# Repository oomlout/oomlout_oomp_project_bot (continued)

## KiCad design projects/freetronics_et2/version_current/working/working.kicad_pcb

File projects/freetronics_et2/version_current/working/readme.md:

# ET2 by freetronics  
This is a harvested standardized copy of a project from github.  
The original project can be found at:  
https://github.com/freetronics/ET2  
Please consult that link for additional, details, files, and license information.  
Note: It was auto harvested and if the original repo had more than one board file or anything out of the ordinary the files here are likely not representative.

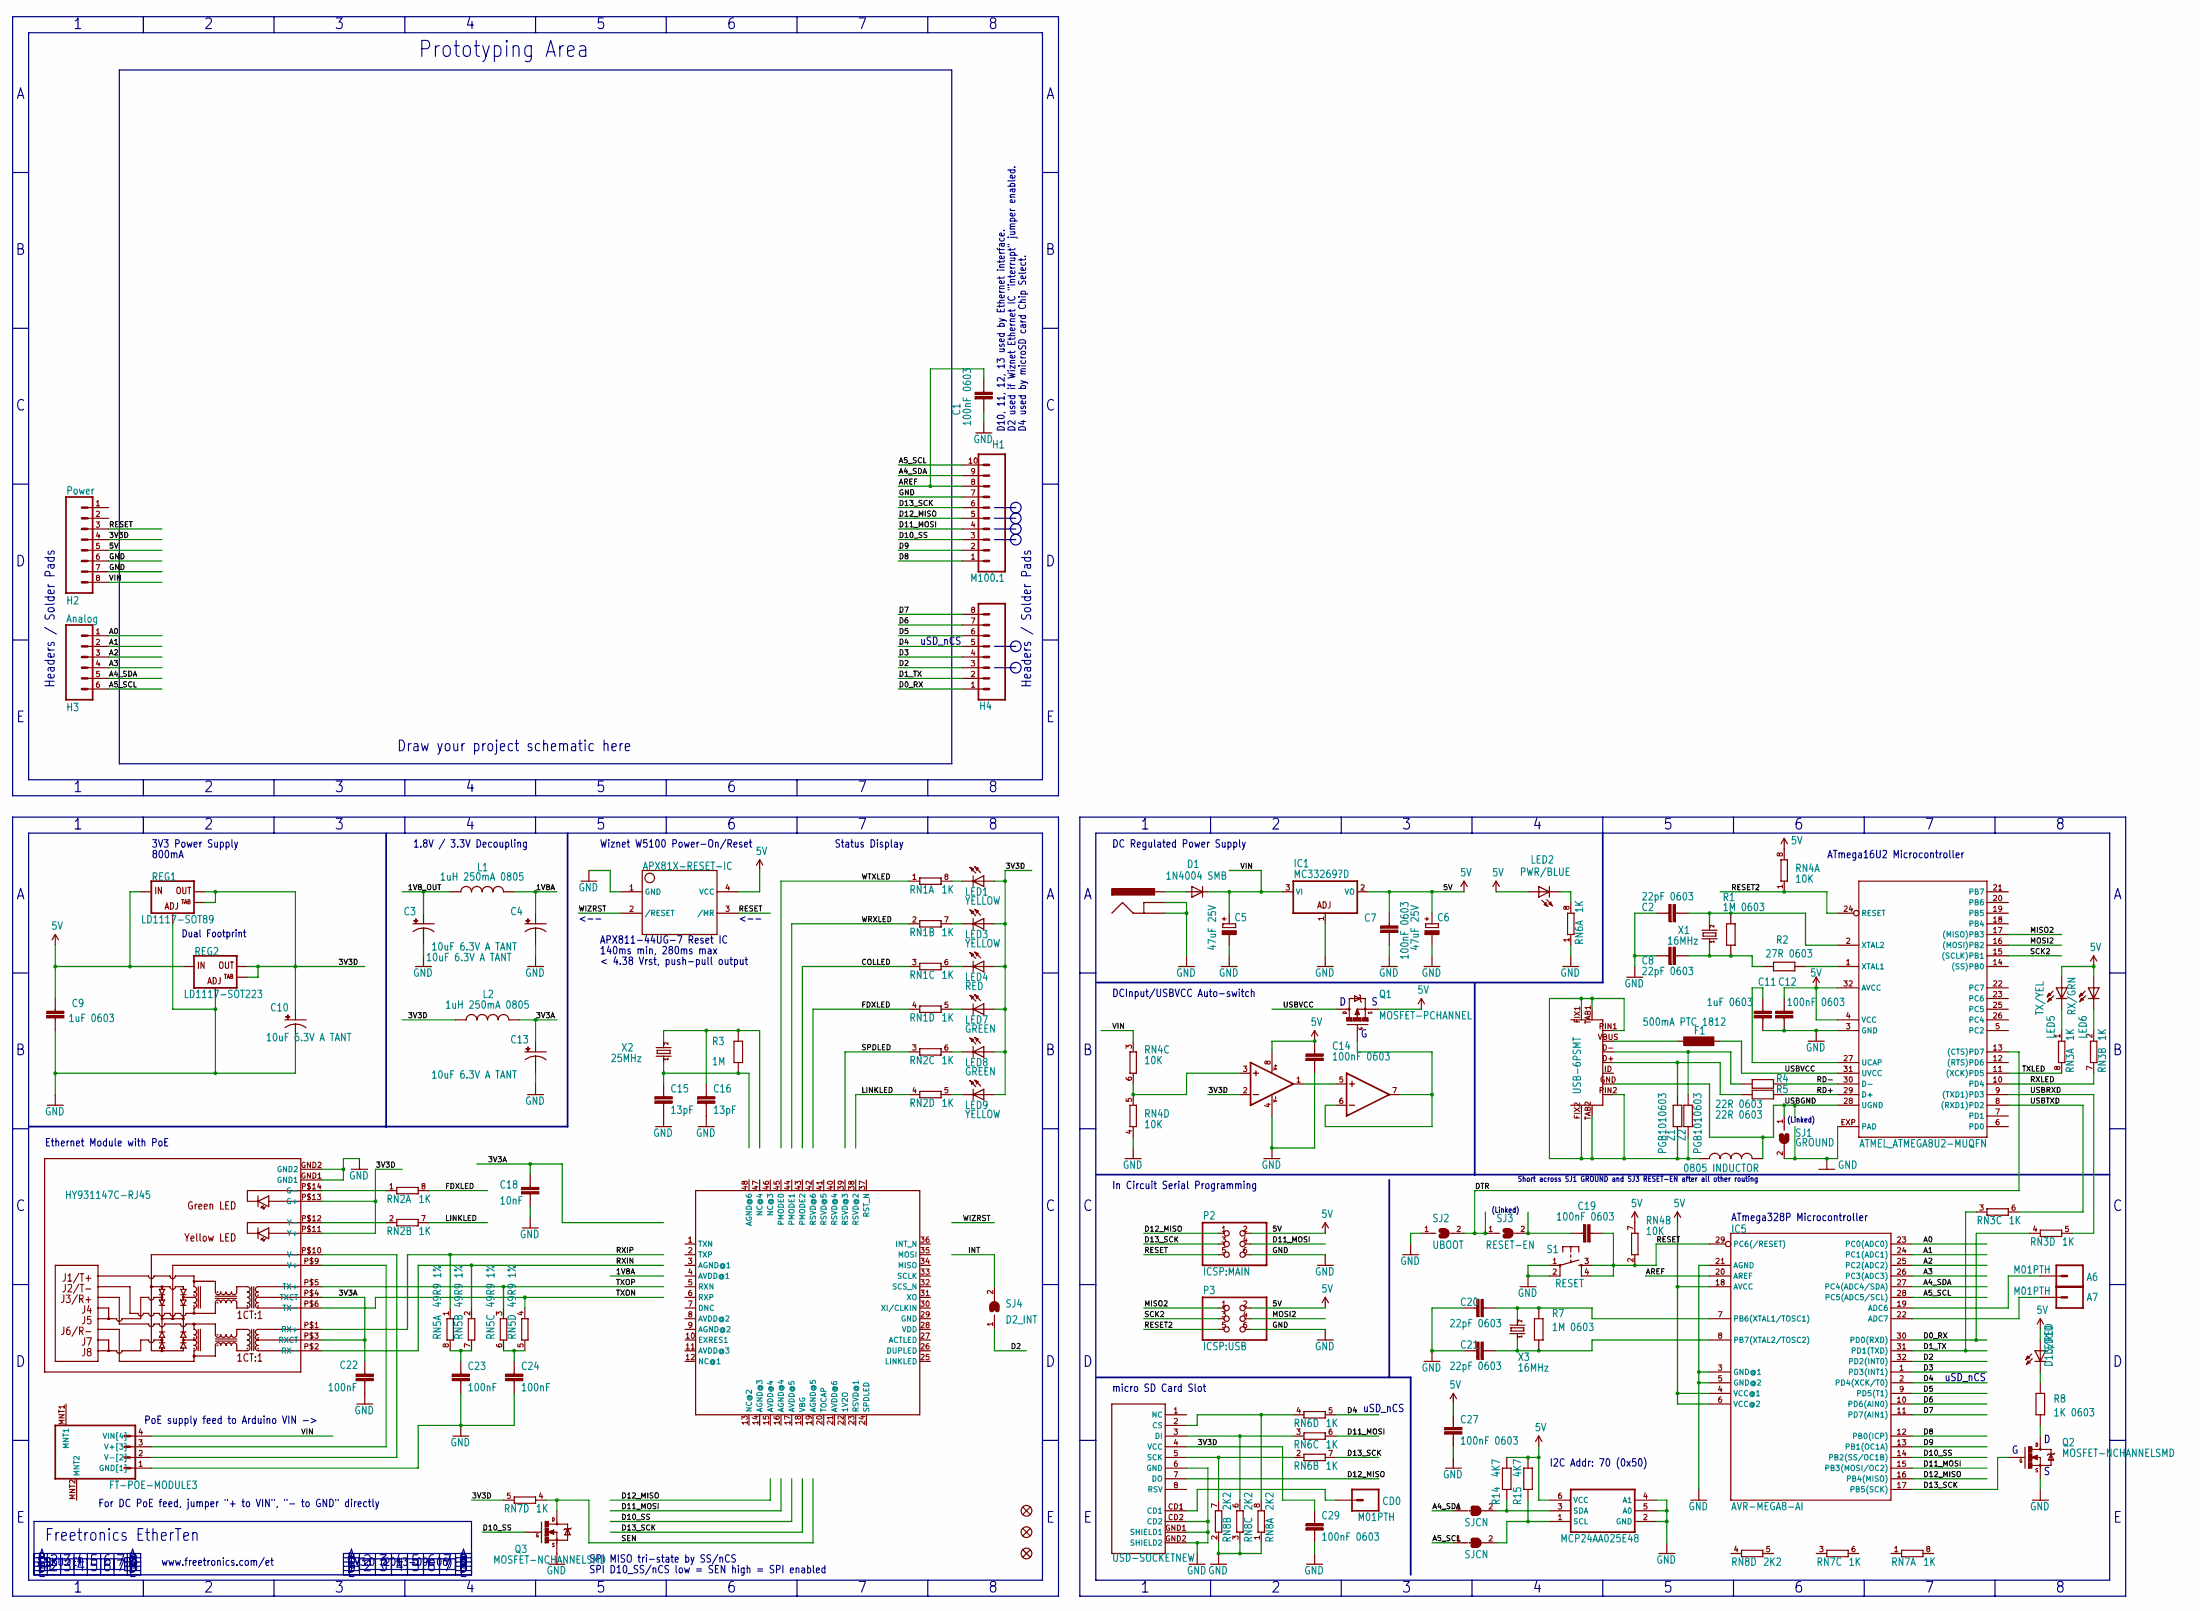
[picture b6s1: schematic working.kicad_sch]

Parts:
A6, A7: M01PTH; 1X01
C1, C7, C12, C14, C19, C27, C29: 100nF 0603; 0603
C2, C8, C20, C21: 22pF 0603; 0603
C3, C4, C10, C13: 10uF 6.3V A TANT; EIA3216
C5, C6: 47uF 25V; PANASONIC_D
C9, C11: 1uF 0603; 0603
C15, C16: 13pF; 0603
C18: 10nF; 0603
C22, C23, C24: 100nF; 0603
CD0: M01PTH; 1X01
D1: 1N4004 SMB; SMB-DIODE
F1: 500mA PTC 1812; L1812
FID1, FID2, FID3: FIDUCIAL1X2.5; FIDUCIAL-1X2.5
H1: M100.1; 1X10
H2: Power; 1X08
H3: Analog; 1X06
H4: Digital_0_7; 1X08
IC1: MC33269?D; DPACK
IC2: APX81X-RESET-IC; SOT143-R
IC3: ATMEL_ATMEGA8U2-MUQFN; ATMEL_QFN32
IC4: LM358D; SO08
IC5: AVR-MEGA8-AI; TQFP32-08
IC7: MCP24AA025E48; SOT23-6
IC8: W5500
J1: POWER_JACKPTH; POWER_JACK_PTH
JP3: FT-POE-MODULE3; FT-POE-MODULE-NOLABEL
L1, L2: 1uH 250mA 0805; L2012C
L3: 0805 INDUCTOR; 0805-LARGE
LED1, LED3, LED9: YELLOW; LED-0603
LED2: PWR/BLUE; LED-0603
LED4: RED; LED-0603
LED5: TX/YEL; LED-0603
LED6: RX/GRN; LED-0603
LED7, LED8: GREEN; LED-0603
LED10: D13/RED; LED-0603
P1: USB-6PSMT; USB-MICROB-MB05PMXX
P2: ICSP:MAIN; 2X03
P3: ICSP:USB; 2X03
P4: USD-SOCKETNEW; MICRO-SD-SOCKET-PP
Q1: MOSFET-PCHANNEL; SOT23
Q2, Q3: MOSFET-NCHANNELSMD; SOT23-3
R1, R7: 1M 0603; 0603
R2: 27R 0603; 0603
R3: 1M; 0603
R4, R5: 22R 0603; 0603
R8: 1K 0603; 0603
R14, R15: 4K7; 0603
REG1: LD1117-SOT89; SOT89
REG2: LD1117-SOT223; SOT223
RN1, RN2, RN3, RN6, RN7: 1K; CAY16
RN4: 10K; CAY16
RN5: 49R9 1%; CAY16
RN8: 2K2; CAY16
S1: RESET; TACTILE_SWITCH_SMD
SJ1: GROUND; SJ
SJ2: UBOOT; SJ
SJ3: RESET-EN; SJ
SJ4: D2_INT; SJ
SJ5, SJ6: SJCN; SJC
U1: HY931147C-RJ45; HY931147C
X1, X3: 16MHz; HC49U-V
X2: 25MHz; HC49U-V
Z1, Z2: PGB1010603; 0603

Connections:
1V8A: C4.A (+), L1.2
1V8_OUT: C3.A (+), L1.1
3V3A: C13.A (+), C18.1, C22.1, L2.2, U1.P$3 (RXCT), U1.P$4 (TXCT)
3V3D: C10.A (+), C29.1, H2.4, IC4.2 (-IN), L2.1, LED1.A, LED3.A, LED4.A, LED7.A, LED8.A, LED9.A, P4.4 (VCC), REG1.2 (OUT), REG1.4 (OUT@1), REG2.2 (OUT), REG2.4 (OUT@1), RN7.5 (2), U1.P$11 (Y+), U1.P$13 (G+)
5V: C6.+, C7.1, C9.1, C12.1, C14.1, C27.1, H2.5, IC1.2 (VO), IC2.4 (VCC), IC3.4 (VCC), IC3.32 (AVCC), IC4.8 (V+), IC5.4 (VCC@1), IC5.6 (VCC@2), IC5.18 (AVCC), IC7.6 (VCC), LED2.A, LED5.A, LED6.A, LED10.A, P2.2, P3.2, Q1.2 (S), R14.1, R15.1, REG1.3 (IN), REG2.3 (IN), RN4.7 (2), RN4.8 (2)
A0: H3.1, IC5.23 (PC0(ADC0))
A1: H3.2, IC5.24 (PC1(ADC1))
A2: H3.3, IC5.25 (PC2(ADC2))
A3: H3.4, IC5.26 (PC3(ADC3))
A4_SDA: H1.9, H3.5, IC5.27 (PC4(ADC4/SDA)), SJ5.1
A5_SCL: H1.10, H3.6, IC5.28 (PC5(ADC5/SCL)), SJ6.1
AREF: C1.1, H1.8, IC5.20 (AREF)
COLLED: RN1.3 (1)
D0_RX: H4.1, IC5.30 (PD0(RXD)), RN3.4 (1)
D1_TX: H4.2, IC5.31 (PD1(TXD)), RN3.3 (1)
D2: H4.3, IC5.32 (PD2(INT0)), SJ4.1
D3: H4.4, IC5.1 (PD3(INT1))
D4: H4.5, IC5.2 (PD4(XCK/T0)), RN6.5 (2)
D5: H4.6, IC5.9 (PD5(T1))
D6: H4.7, IC5.10 (PD6(AIN0))
D7: H4.8, IC5.11 (PD7(AIN1))
D8: H1.1, IC5.12 (PB0(ICP))
D9: H1.2, IC5.13 (PB1(OC1A))
D10_SS: H1.3, IC5.14 (PB2(SS/OC1B)), Q3.1 (G)
D11_MOSI: H1.4, IC5.15 (PB3(MOSI/OC2)), P2.4, RN6.6 (2)
D12_MISO: H1.5, IC5.16 (PB4(MISO)), P2.1, P4.7 (DO)
D13_SCK: H1.6, IC5.17 (PB5(SCK)), P2.3, Q2.1 (G), RN6.7 (2)
DTR: IC3.13 ((CTS)PD7), SJ2.2, SJ3.1
FDXLED: RN1.4 (1), RN2.8 (2)
GND: C1.2, C2.1, C3.C (-), C4.C (-), C5.-, C6.-, C7.2, C8.1, C9.2, C10.C (-), C11.2, C12.2, C13.C (-), C14.2, C15.2, C16.2, C18.2, C20.1, C21.1, C22.2, C23.2, C24.2, C27.2, C29.2, H1.7, H2.6, H2.7, IC1.1 (ADJ), IC2.1 (GND), IC3.3 (GND), IC3.EXP (PAD), IC4.4 (V-), IC5.3 (GND@1), IC5.5 (GND@2), IC5.21 (AGND), IC7.2 (GND), IC7.4 (A1), IC7.5 (A0), J1.GND, J1.GNDBREAK, JP3.1 (GND[1]), P2.6, P3.6, P4.6 (GND), P4.CD2, P4.GND1 (SHIELD1), P4.GND2 (SHIELD2), Q2.2 (S), Q3.2 (S), REG1.1 (ADJ), REG2.1 (ADJ), RN4.4 (1), RN6.1, RN8.1, RN8.2 (1), RN8.3 (1), S1.1, S1.2, SJ1.2, SJ2.1, U1.GND1, U1.GND2
INT: SJ4.2
LINKLED: RN2.4 (1), RN2.7 (2)
MISO2: IC3.17 ((MISO)PB3), P3.1
MOSI2: IC3.16 ((MOSI)PB2), P3.4
unnamed: C24.1, RN5.5 (2), RN5.6 (2)
unnamed: C20.2, IC5.7 (PB6(XTAL1/TOSC1)), R7.2, X3.2
unnamed: C19.1, SJ3.2
unnamed: LED10.C, R8.2
unnamed: IC7.1 (SCL), R15.2, SJ6.2
unnamed: Q2.3 (D), R8.1
unnamed: C21.2, IC5.8 (PB7(XTAL2/TOSC2)), R7.1, X3.1
unnamed: IC3.1 (XTAL1), R2.1
unnamed: L3.1, P1.FIX1, P1.FIX2, P1.PIN1, P1.PIN2, P1.TAB1, P1.TAB2, Z1.2, Z2.2
unnamed: LED6.C, RN3.2 (1)
unnamed: IC4.3 (+IN), RN4.5 (2), RN4.6 (2)
unnamed: LED5.C, RN3.1
unnamed: LED2.C, RN6.8 (2)
unnamed: P1.D+, R5.2, Z1.1
unnamed: P1.D-, R4.2, Z2.1
unnamed: IC4.6 (-IN), IC4.7 (OUT), Q1.1 (G)
unnamed: IC4.1 (OUT), IC4.5 (+IN)
unnamed: P4.2 (CS), RN6.4 (1), RN8.8 (2)
unnamed: A7.1, IC5.22 (ADC7)
unnamed: A6.1, IC5.19 (ADC6)
unnamed: CD0.1, P4.CD1
unnamed: P4.5 (SCK), RN6.2 (1), RN8.7 (2)
unnamed: P4.3 (DI), RN6.3 (1), RN8.6 (2)
unnamed: LED8.C, RN2.6 (2)
unnamed: LED9.C, RN2.5 (2)
unnamed: IC7.3 (SDA), R14.2, SJ5.2
unnamed: D1.A, J1.PWR
unnamed: RN2.1, U1.P$14 (G-)
unnamed: JP3.3 (V+[3]), U1.P$9 (V+)
unnamed: JP3.2 (V-[2]), U1.P$10 (V-)
unnamed: C2.2, IC3.2 (XTAL2), R1.2, X1.2
unnamed: C8.2, R1.1, R2.2, X1.1
unnamed: F1.1, P1.VBUS
unnamed: C11.1, IC3.27 (UCAP)
unnamed: C23.1, RN5.7 (2), RN5.8 (2)
unnamed: LED7.C, RN1.5 (2)
unnamed: LED4.C, RN1.6 (2)
unnamed: LED3.C, RN1.7 (2)
unnamed: LED1.C, RN1.8 (2)
unnamed: RN2.2 (1), U1.P$12 (Y-)
RD+: IC3.29 (D+), R5.1
RD-: IC3.30 (D-), R4.1
RESET: C19.2, H2.3, IC2.3 (/MR), IC5.29 (PC6(/RESET)), P2.5, RN4.2 (1), S1.3, S1.4
RESET2: IC3.24 (RESET), P3.5, RN4.1
RXIN: RN5.2 (1), U1.P$2 (RX-)
RXIP: RN5.1, U1.P$1 (RX+)
RXLED: IC3.10 (PD4), RN3.7 (2)
SCK2: IC3.15 ((SCLK)PB1), P3.3
SEN: Q3.3 (D), RN7.4 (1)
SPDLED: RN2.3 (1)
TXLED: IC3.11 ((XCK)PD5), RN3.8 (2)
TXON: RN5.4 (1), U1.P$6 (TX-)
TXOP: RN5.3 (1), U1.P$5 (TX+)
USBGND: IC3.28 (UGND), L3.2, P1.GND, SJ1.1
USBRXD: IC3.9 ((TXD1)PD3), RN3.5 (2)
USBTXD: IC3.8 ((RXD1)PD2), RN3.6 (2)
USBVCC: F1.2, IC3.31 (UVCC), Q1.3 (D)
VIN: C5.+, D1.C, H2.8, IC1.3 (VI), JP3.4 (VIN[4]), RN4.3 (1)
WIZRST: IC2.2 (/RESET)
WRXLED: RN1.2 (1)
WTXLED: RN1.1
XTLN: C16.1, R3.2, X2.2
XTLP: C15.1, R3.1, X2.1

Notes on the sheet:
Prototyping Area
(Linked)
D4 used by microSD card Chip Select.
Dual Footprint
SKU: ET
Status Display
Headers / Solder Pads
Freetronics EtherTen
uSD_nCS
V3.0 (2013-09-06)
In Circuit Serial Programming
micro SD Card Slot
www.freetronics.com/et
SPI MISO tri-state by SS/nCS
APX811-44UG-7 Reset IC
Ethernet Module with PoE
1.8V / 3.3V Decoupling
For DC PoE feed, jumper "+ to VIN", "- to GND" directly
DC Regulated Power Supply
<--
ATmega328P Microcontroller
Short across SJ1 GROUND and SJ3 RESET-EN after all other routing
I2C Addr: 70 (0x50)
PoE supply feed to Arduino VIN ->
3V3 Power Supply
D2 used if Wiznet Ethernet IC "interrupt" jumper enabled.
SPI D10_SS/nCS low = SEN high = SPI enabled
Wiznet W5100 Power-On/Reset
Draw your project schematic here
800mA
< 4.38 Vrst, push-pull output
D10, 11, 12, 13 used by Ethernet interface.
DCInput/USBVCC Auto-switch
140ms min, 280ms max
ATmega16U2 Microcontroller

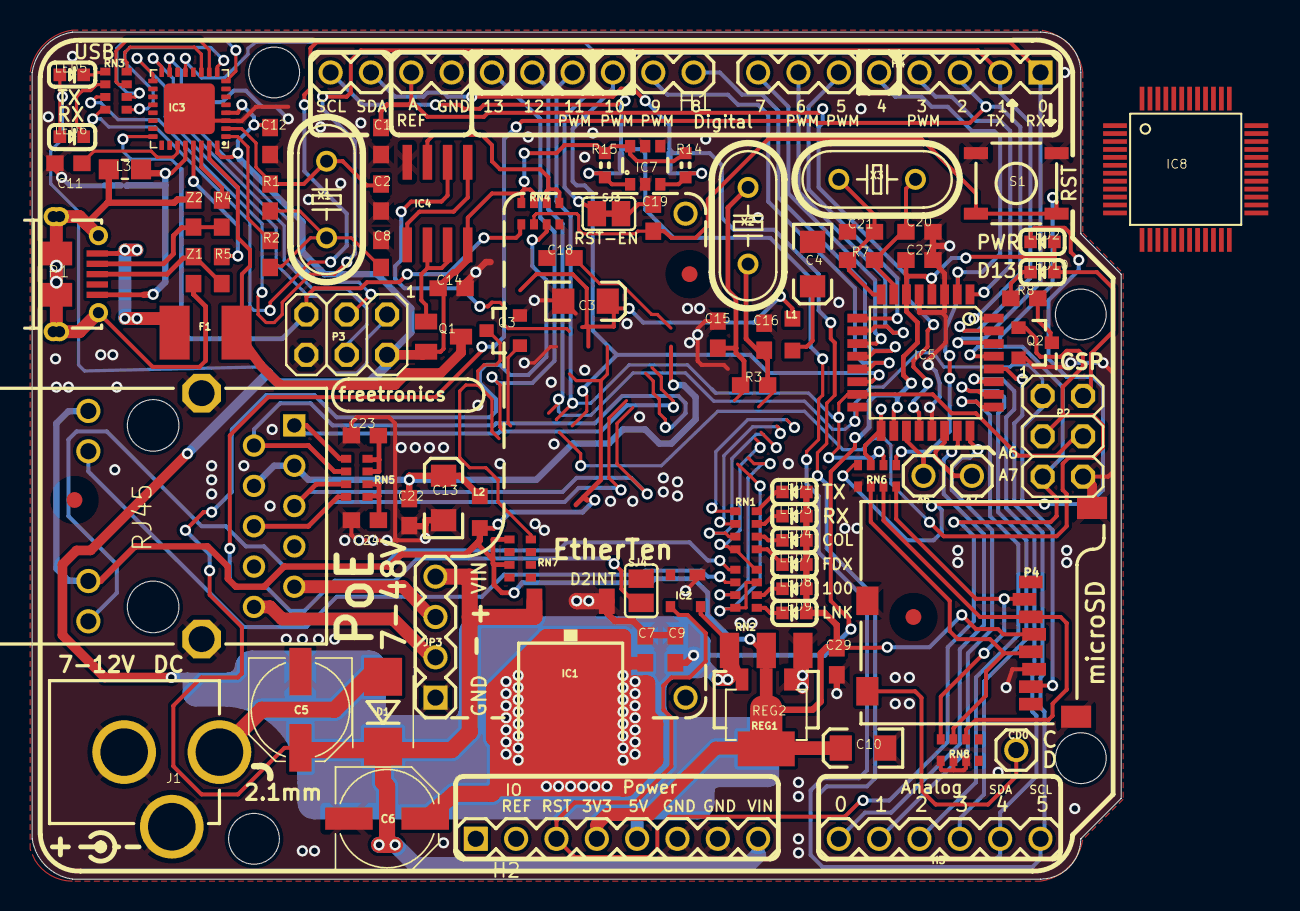
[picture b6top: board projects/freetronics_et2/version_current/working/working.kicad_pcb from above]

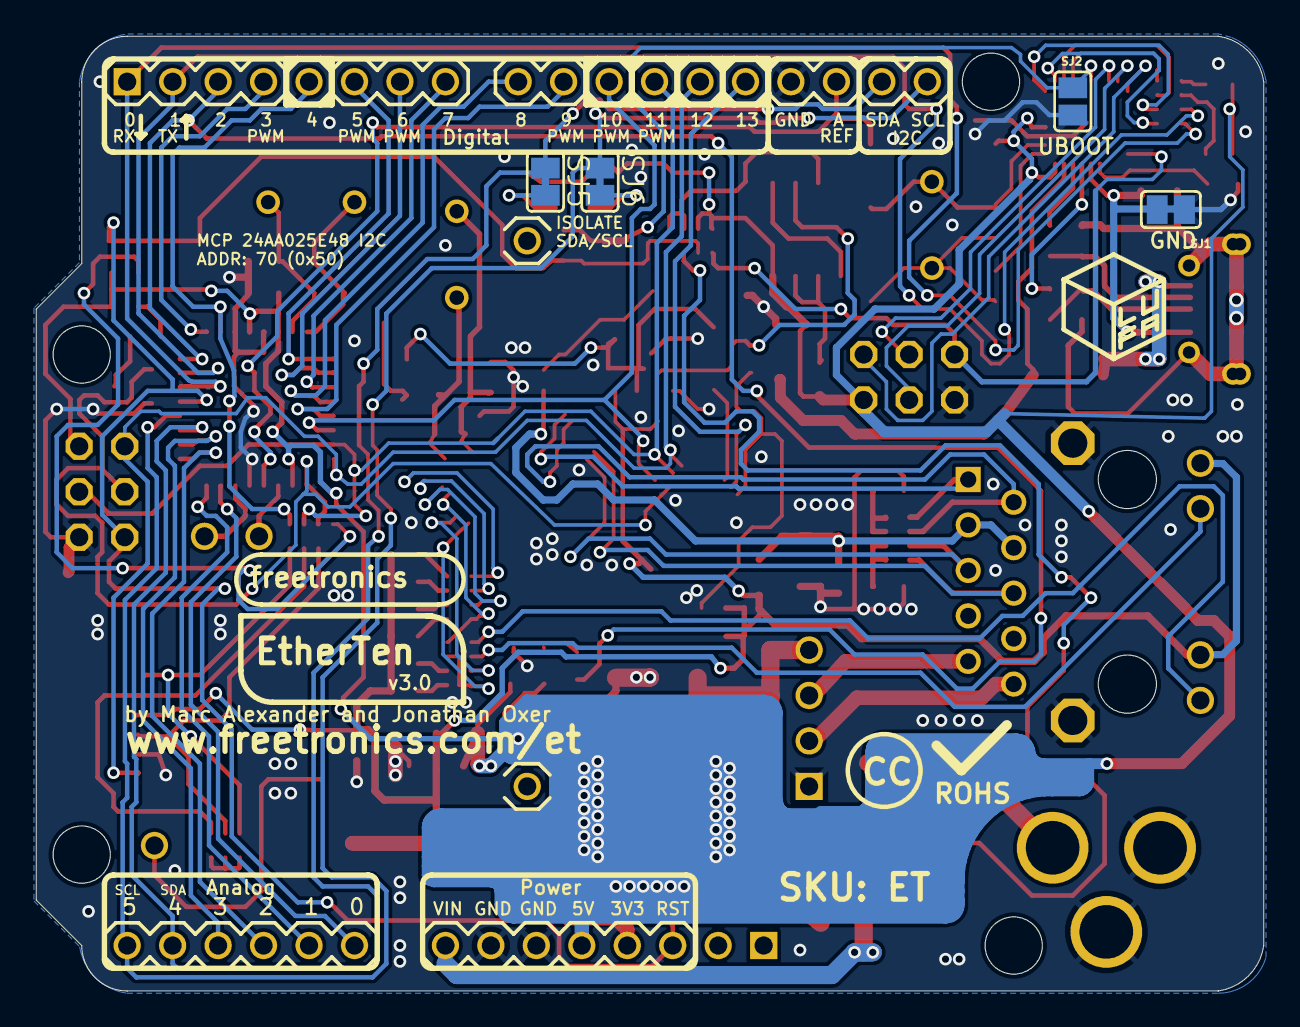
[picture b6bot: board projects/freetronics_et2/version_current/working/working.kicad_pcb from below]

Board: 2 copper layers, 68.6 x 53.3 mm, 102 parts (4 on the bottom side), 91 nets.

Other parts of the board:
@HOLE0, @HOLE1, @HOLE2, @HOLE3: (no value)

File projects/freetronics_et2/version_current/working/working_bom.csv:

"Id";"Designator";"Footprint";"Quantity";"Designation";"Supplier and ref";
1;"P1";"USB-MICROB-MB05PMXX";1;"USB-6PSMT";;;
2;"C15,C16";"0603";2;"13pF";;;
3;"C23,C24,C22";"0603";3;"100nF";;;
4;"J1";"POWER_JACK_PTH";1;"DC_2_1MM";;;
5;"C13,C10,C3,C4";"EIA3216";4;"10uF 6.3V A TANT";;;
6;"L2,L1";"L2012C";2;"1uH 250mA 0805";;;
7;"C6,C5";"PANASONIC_D";2;"47uF 25V";;;
8;"R2";"0603";1;"27R 0603";;;
9;"R7,R1";"0603";2;"1M 0603";;;
10;"LED4";"LED-0603";1;"RED";;;
11;"LED5";"LED-0603";1;"TX/YEL";;;
12;"IC7";"SOT23-6";1;"MCP24AA025E48";;;
13;"IC3";"ATMEL_QFN32";1;"ATMEGA16U2-MU";;;
14;"Z1,Z2";"0603";2;"PGB1010603";;;
15;"RN1,RN3,RN7,RN2,RN6";"CAY16";5;"1K";;;
16;"LED9,LED3,LED1";"LED-0603";3;"YELLOW";;;
17;"R14,R15";"0603";2;"4K7";;;
18;"X1,X3";"HC49U-V";2;"16MHz";;;
19;"C7,C29,C19,C27,C1,C14,C12";"0603";7;"100nF 0603";;;
20;"A7,CD0,A6";"1X01";3;"M01PTH";;;
21;"C9,C11";"0603";2;"1uF 0603";;;
22;"@HOLE1,@HOLE0,@HOLE3,@HOLE2";"";4;"";;;
23;"S1";"TACTILE_SWITCH_SMD";1;"RESET";;;
24;"C18";"0603";1;"10nF";;;
25;"FID1,FID2,FID3";"FIDUCIAL-1X2.5";3;"FIDUCIAL1X2.5";;;
26;"LED7,LED8";"LED-0603";2;"GREEN";;;
27;"P2";"2X03";1;"ICSP:MAIN";;;
28;"REG1";"SOT89";1;"LD1117-SOT89";;;
29;"LED6";"LED-0603";1;"RX/GRN";;;
30;"C21,C2,C20,C8";"0603";4;"22pF 0603";;;
31;"IC5";"TQFP32-08";1;"ATMEGA328P TQFP32";;;
32;"Q1";"SOT23";1;"FDN340P";;;
33;"SJ3";"SJ";1;"RESET-EN";;;
34;"R8";"0603";1;"1K 0603";;;
35;"H2";"1X08";1;"Power";;;
36;"SJ4";"SJ";1;"D2_INT";;;
37;"H3";"1X06";1;"Analog";;;
38;"LED2";"LED-0603";1;"PWR/BLUE";;;
39;"R3";"0603";1;"1M";;;
40;"IC8";"W5500";1;"W5500";;;
41;"L3";"0805-LARGE";1;"0805 INDUCTOR";;;
42;"RN5";"CAY16";1;"49R9 1%";;;
43;"P4";"MICRO-SD-SOCKET-PP";1;"microSD";;;
44;"IC4";"SO08";1;"LM358D";;;
45;"H4";"1X08";1;"Digital_0_7";;;
46;"X2";"HC49U-V";1;"25MHz";;;
47;"JP3";"FT-POE-MODULE-NOLABEL";1;"FT-POE-MODULE3";;;
48;"LED10";"LED-0603";1;"D13/RED";;;
49;"R5,R4";"0603";2;"22R 0603";;;
50;"IC2";"SOT143-R";1;"APX811-44UG-7";;;
51;"RN4";"CAY16";1;"10K";;;
52;"RN8";"CAY16";1;"2K2";;;
53;"P3";"2X03";1;"ICSP:USB";;;
54;"IC1";"DPACK";1;"MC33269DT-5.0";;;
55;"F1";"L1812";1;"500mA PTC 1812";;;
56;"Q3,Q2";"SOT23-3";2;"2N7002";;;
57;"D1";"SMB-DIODE";1;"1N4004 SMB";;;
58;"H1";"1X10";1;"Digital_8_13";;;
59;"U1";"HY931147C";1;"HY931147C-RJ45";;;
60;"REG2";"SOT223";1;"LD1117-SOT223";;;
61;"SJ2";"SJ";1;"UBOOT";;;
62;"SJ1";"SJ";1;"GROUND";;;
63;"SJ6,SJ5";"SJC";2;"";;;
